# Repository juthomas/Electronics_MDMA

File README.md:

# MEGA DRINKING MACHINA ADVENTURE

<br/>

__Sommaire__ :
* [Description](#description)
* [Installation](#installation-avr)
* [Usage](#usage)
* [Visual Studio Code Linter](#visual-studio-code-linter)
* [Project Functionalities](#project-functionalities)
  * [Leds Control](#leds-control)
  * [Prerequisites](#prerequisites)
  * [Leds Variables](#leds-variables)
  * [Color Attribution](#color-attribution)
  * [Usefull Functions](#usefull-functions)

<div id='description'/>

## Description

Cet objet à été conçu sur les bases d’un témoignage perturbant à la date du 27 juin 2007 sur le forum ████ par l’utilisateur Chri████4.
Il y fait mention d’un jeu à boire avec ses amis où ils auraient décidé d'invoquer Satan aux alentours de 23h42. La soirée aurait tourné en une cruelle mission de subjugation du malin avec pour seule arme l’alcool en grande quantité qu’ils avaient préparé pour faire la fête. Suite à cette affaire le service d’exorcisme V-696 (avec à sa tête Jean-███II) aurait procédé à une énorme commande de Sobieski. 

À travers le projet Mega Drinking Machina Adventure™ nous voulons faire vivre à nos très chers futurs utilisateurs une simulation familiale de cette aventure hors du commun. Une compilation de jeux à boire allant de 1 à 5 joueurs sera proposée, avec une mise en place intuitive et rapide. Sur batterie, lumineux et facile à transporter, il deviendra votre meilleur outil pour pimenter vos soirées peu importe le contexte.
<div id='installation-avr'/>

## Installation (AVR)

* Debian Based Linux :  
  * Install avr-gcc :  
  `sudo apt-get install gcc-avr binutils-avr avr-libc`
  * Install avr-dude :  
  `sudo apt-get install avrdude`
* Macos Unix :  
  * Install brew (for noobies) :  
  `rm -rf $HOME/.brew && git clone --depth=1 https://github.com/Homebrew/brew $HOME/.brew && export PATH=$HOME/.brew/bin:$PATH && brew update && echo "export PATH=$HOME/.brew/bin:$PATH" >> ~/.zshrc`
  * Install avr-gcc :  
  `brew tap osx-cross/avr`  
  `brew install avr-gcc`
  * Install avr-dude :  
  `brew install avrdude`
<div id='usage'/>

## Usage

* Setup port :  
  `ls /dev/ > /tmp/file1`  
  then connect board  
  `ls /dev/ > /tmp/file2`  
  `diff /tmp/file1 /tmp/file2`  
  will give you the port  
  paste the given port to the `PORT` variable of the makefile

* Upload to board :  
  `make coffee` for build and upload  
  `make debug` for debuging  
  `make help` for other options
<div id='visual-studio-code-linter'/>

## Visual Studio Code Linter

* Install C/C++ extension  
* Configure C/C++ extension for avr :  
  Type `C/C++: Edit Configurations (JSON)` in Command Palette  
  * Linux :  
  Add `"/usr/lib/avr/include/**"` line to includePath  
  * Macos :  
  Add `"/Users/tmp/.brew/Cellar/avr-gcc@9/9.3.0_2/avr/include/**"`  
  on labelec macs  
  or  
  `/System/Volumes/Data/usr/local/Cellar/avr-gcc@9/9.3.0_2/avr/include/**`  
  (on real macs)  
  to includePath.  
  If this line doesnt work find "avr/io.h" file with `find / -name io.h`  
  Add the containing folder to includePath (like Linux method)

<div id='project-functionalities'/>

## Project Functionalities

<div id='leds-control'/>

### Leds Control

<div id='prerequisites'/>

#### Prerequisites
* `ft_pin_mode(led_pin, FT_OUTPUT);`

<div id='leds-variables'/>

#### Leds Variables
* char buffer (size = number of leds * 3)

<div id='color-attribution'/>

#### Color Attribution
  The color format is uint32_t : `0xLLRRGGBB`  
  LL : Luminosity (0x01 to 0xFF, or 0x00 to ignore)  
  RR : Red (0x00 to 0xFF)  
  GG : Green (0x00 to 0xFF)  
  BB : Blue (0x00 to 0xFF)  

<div id='usefull-functions'/>

#### Usefull Functions
* `uint8_t *feed_one_pixel(uint16_t pixel_index, uint8_t *pixels, uint32_t color)`  
  feed the selected pixel with the color
* `led_send_data(51, pixels, pixels_number);`  
  send data to the leds

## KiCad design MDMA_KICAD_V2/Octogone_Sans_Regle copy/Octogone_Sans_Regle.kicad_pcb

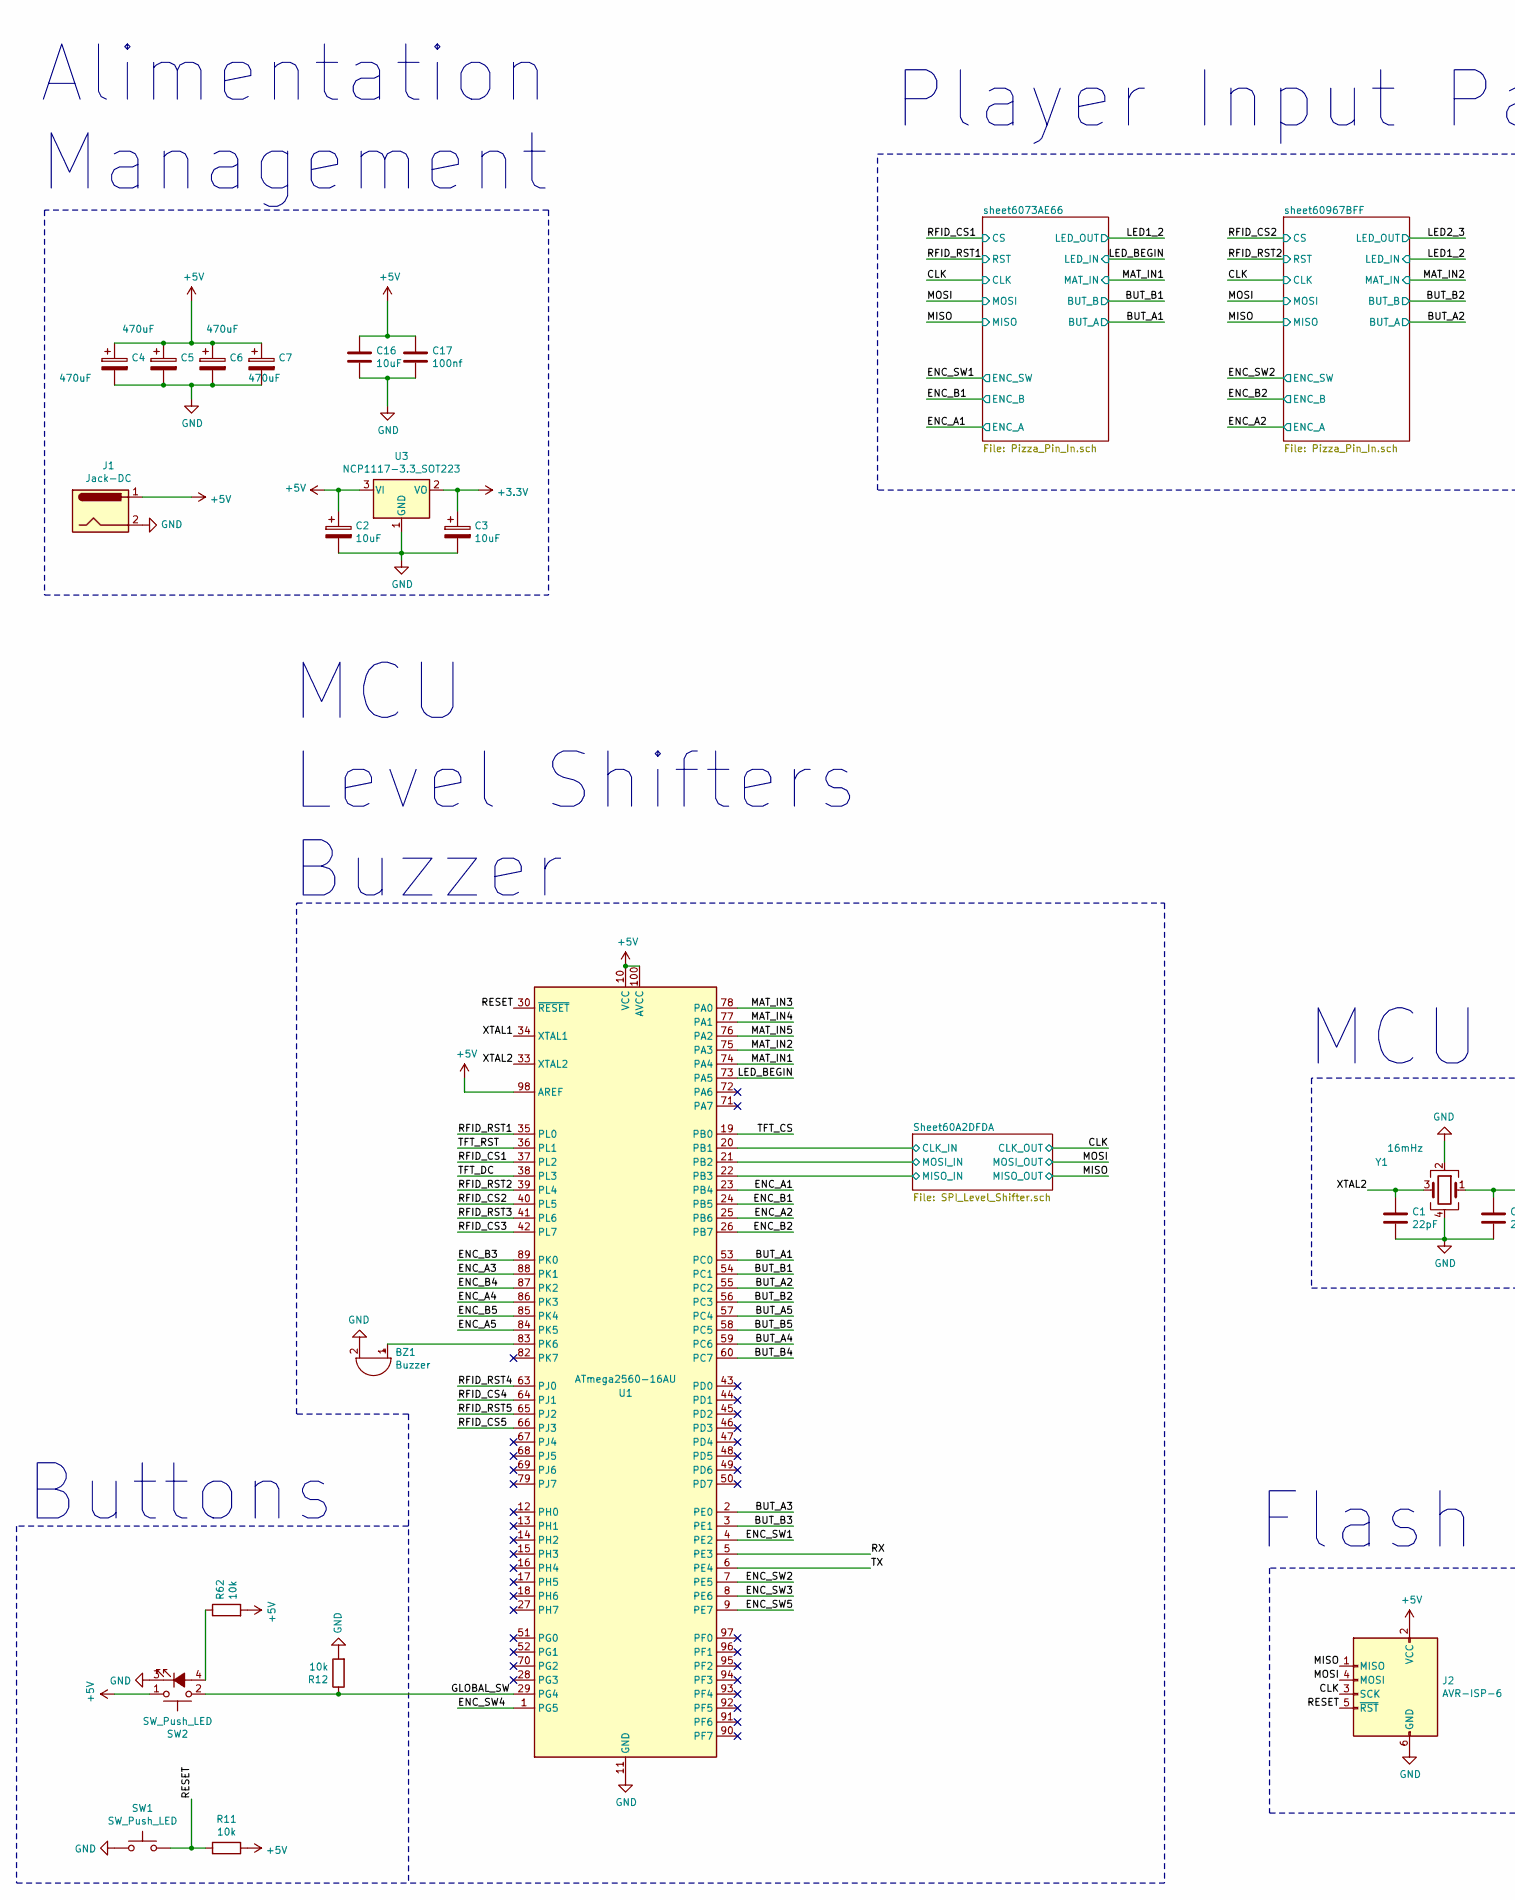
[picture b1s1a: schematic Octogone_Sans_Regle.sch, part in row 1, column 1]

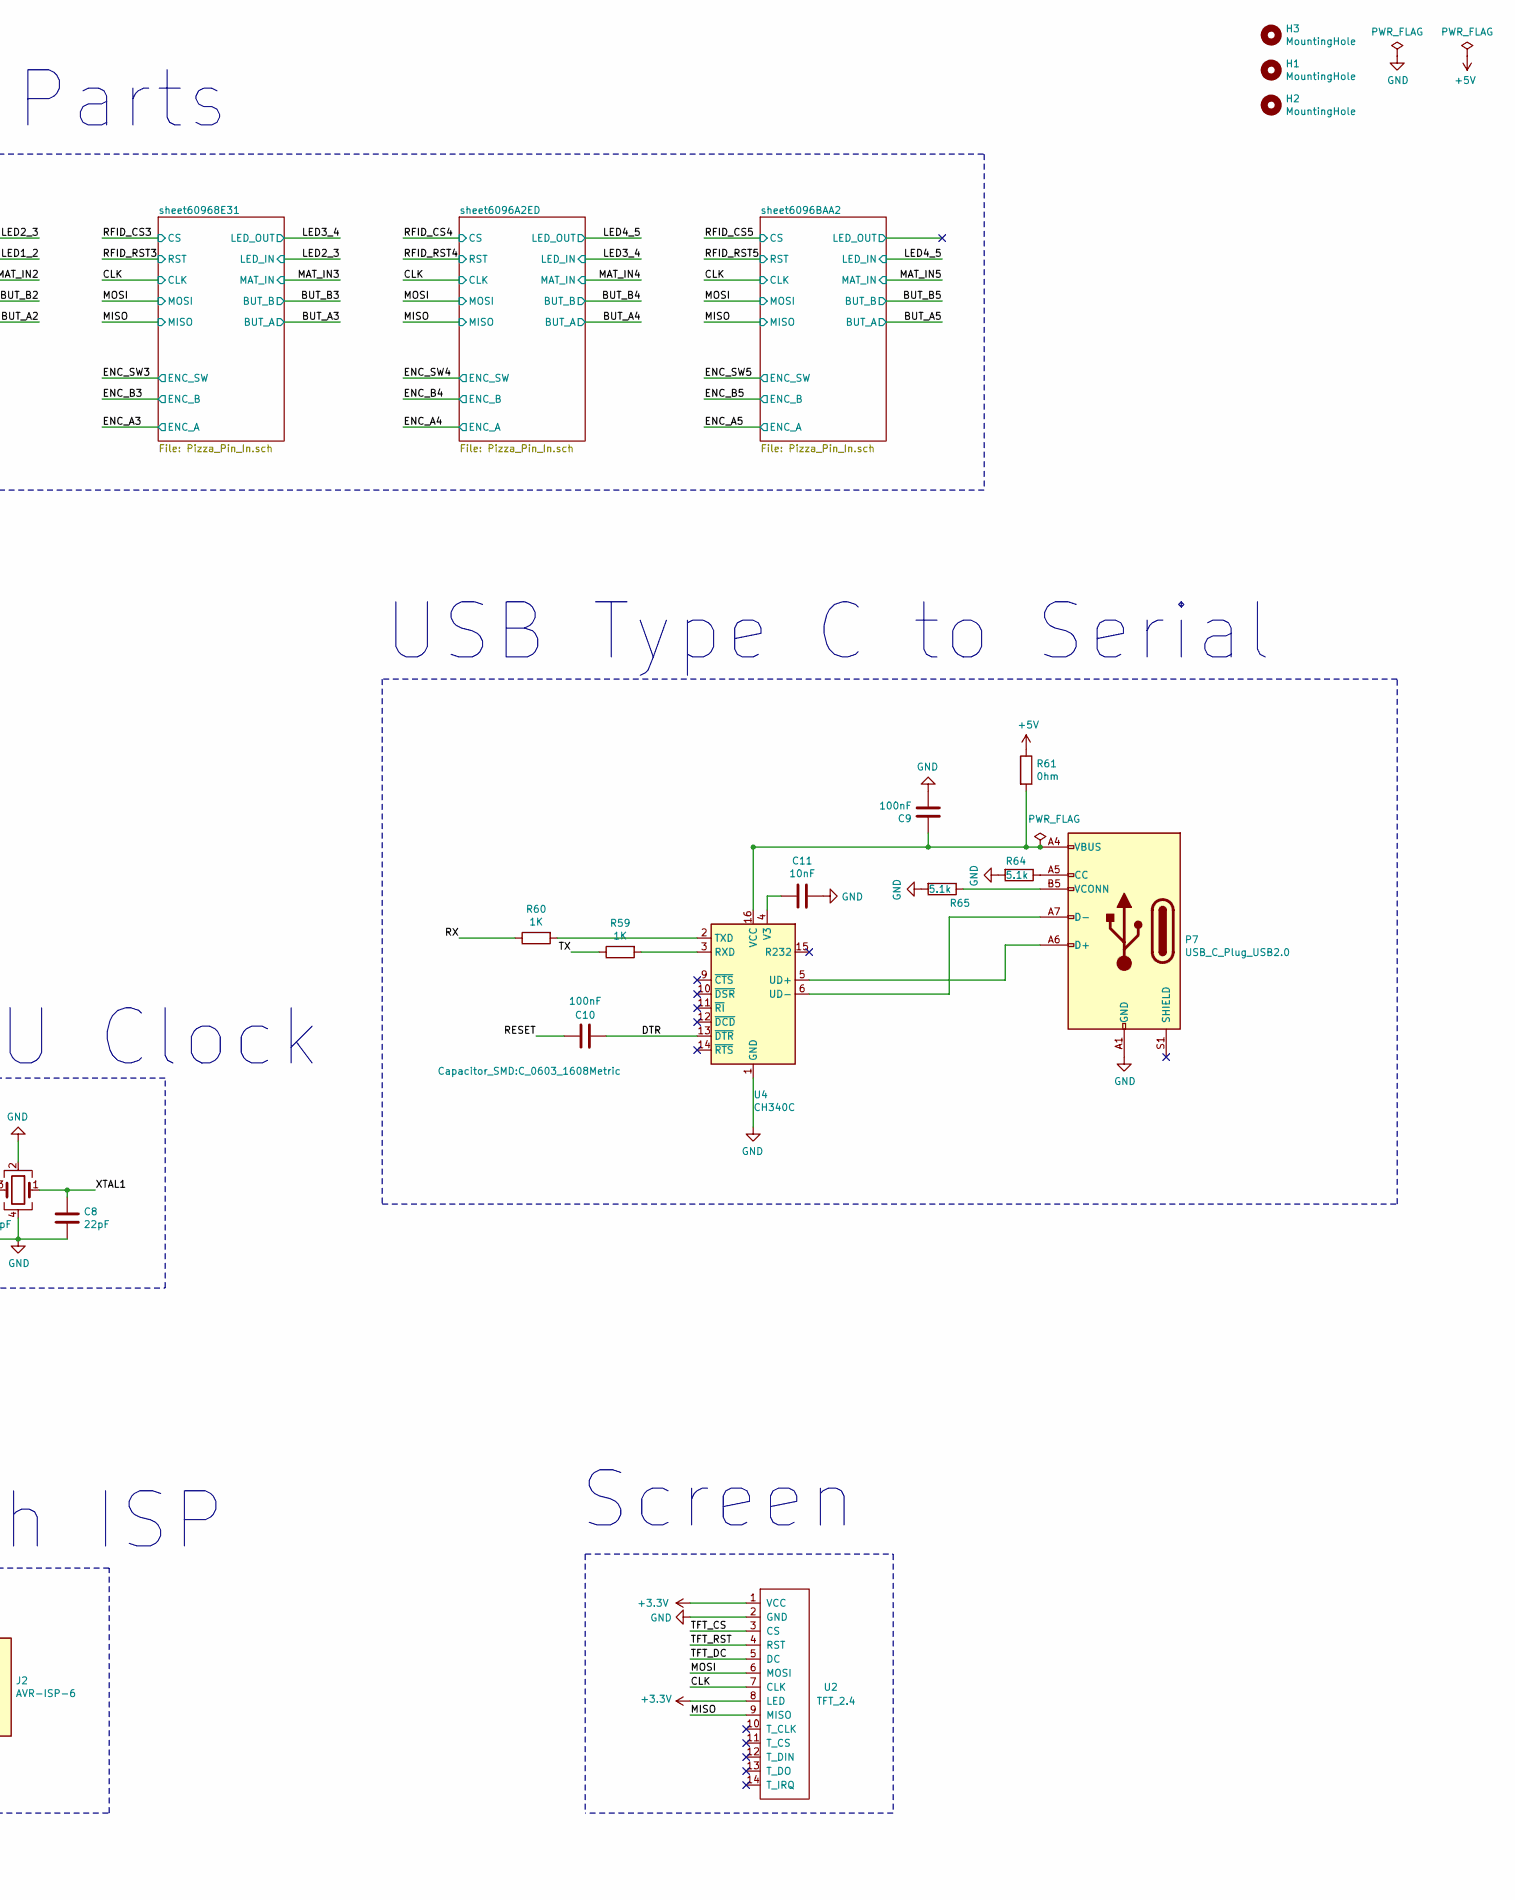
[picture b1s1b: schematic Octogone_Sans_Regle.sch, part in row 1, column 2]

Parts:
BZ1: Buzzer; Buzzer_12x9.5RM7.6
C1, C8: 22pF; C_0603_1608Metric
C2, C3: 10uF; CP_EIA-3216-18_Kemet-A
C4, C5, C6, C7: 470uF; CP_EIA-7343-30_AVX-N
C9, C10: 100nF; C_0603_1608Metric
C11: 10nF; C_0603_1608Metric
C16: 10uF; C_0603_1608Metric
C17: 100nf; C_0603_1608Metric
H1, H2, H3: MountingHole; MountingHole_3.2mm_M3
J1: Jack-DC; BarrelJack_Horizontal
J2: AVR-ISP-6; Connector_SPI_6
P7: USB_C_Plug_USB2.0; USB_C_Receptacle_HRO_TYPE-C-31-M-12
R11, R12, R62: 10k; R_0603_1608Metric
R59, R60: 1K; R_0603_1608Metric
R61: 0hm; R_0603_1608Metric
R64, R65: 5.1k; R_0603_1608Metric
SW1: SW_Push_LED; Switch_4x3
SW2: SW_Push_LED; SW_LED_16mm
U1: ATmega2560-16AU; TQFP-100_14x14mm_P0.5mm
U2: TFT_2.4; TFT_Connector
U3: NCP1117-3.3_SOT223; SOT-223-3_TabPin2
U4: CH340C; SOIC-16_3.9x9.9mm_P1.27mm
Y1: 16mHz; crystal

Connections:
+3V3: C3.1, U2.1 (VCC), U2.8 (LED), U3.2 (VO); also elsewhere on the board
+5V: C2.1, C4.1, C5.1, C6.1, C7.1, C16.1, C17.1, J1.1, J2.2 (VCC), R11.1, R61.1, R62.2, SW2.1, U1.10 (VCC), U1.31 (VCC), U1.61 (VCC), U1.80 (VCC), U1.98 (AREF), U1.100 (AVCC), U3.3 (VI); also elsewhere on the board
/BUT_A1: U1.53 (PC0); also elsewhere on the board
/BUT_A2: U1.55 (PC2); also elsewhere on the board
/BUT_A3: U1.2 (PE0); also elsewhere on the board
/BUT_A4: U1.59 (PC6); also elsewhere on the board
/BUT_A5: U1.57 (PC4); also elsewhere on the board
/BUT_B1: U1.54 (PC1); also elsewhere on the board
/BUT_B2: U1.56 (PC3); also elsewhere on the board
/BUT_B3: U1.3 (PE1); also elsewhere on the board
/BUT_B4: U1.60 (PC7); also elsewhere on the board
/BUT_B5: U1.58 (PC5); also elsewhere on the board
/CLK: J2.3 (SCK), U2.7 (CLK); also elsewhere on the board
/DTR: C10.2, U4.13 (~DTR)
/ENC_A1: U1.23 (PB4); also elsewhere on the board
/ENC_A2: U1.25 (PB6); also elsewhere on the board
/ENC_A3: U1.88 (PK1); also elsewhere on the board
/ENC_A4: U1.86 (PK3); also elsewhere on the board
/ENC_A5: U1.84 (PK5); also elsewhere on the board
/ENC_B1: U1.24 (PB5); also elsewhere on the board
/ENC_B2: U1.26 (PB7); also elsewhere on the board
/ENC_B3: U1.89 (PK0); also elsewhere on the board
/ENC_B4: U1.87 (PK2); also elsewhere on the board
/ENC_B5: U1.85 (PK4); also elsewhere on the board
/ENC_SW1: U1.4 (PE2); also elsewhere on the board
/ENC_SW2: U1.7 (PE5); also elsewhere on the board
/ENC_SW3: U1.8 (PE6); also elsewhere on the board
/ENC_SW4: U1.1 (PG5); also elsewhere on the board
/ENC_SW5: U1.9 (PE7); also elsewhere on the board
/GLOBAL_SW: R12.1, SW2.2, U1.29 (PG4)
/LED_BEGIN: U1.73 (PA5); also elsewhere on the board
/MAT_IN1: U1.74 (PA4); also elsewhere on the board
/MAT_IN2: U1.75 (PA3); also elsewhere on the board
/MAT_IN3: U1.78 (PA0); also elsewhere on the board
/MAT_IN4: U1.77 (PA1); also elsewhere on the board
/MAT_IN5: U1.76 (PA2); also elsewhere on the board
/MISO: J2.1 (MISO), U2.9 (MISO); also elsewhere on the board
/MOSI: J2.4 (MOSI), U2.6 (MOSI); also elsewhere on the board
/RESET: C10.1, J2.5 (~RST), R11.2, SW1.2, U1.30 (~RESET)
/RFID_CS1: U1.37 (PL2); also elsewhere on the board
/RFID_CS2: U1.40 (PL5); also elsewhere on the board
/RFID_CS3: U1.42 (PL7); also elsewhere on the board
/RFID_CS4: U1.64 (PJ1); also elsewhere on the board
/RFID_CS5: U1.66 (PJ3); also elsewhere on the board
/RFID_RST1: U1.35 (PL0); also elsewhere on the board
/RFID_RST2: U1.39 (PL4); also elsewhere on the board
/RFID_RST3: U1.41 (PL6); also elsewhere on the board
/RFID_RST4: U1.63 (PJ0); also elsewhere on the board
/RFID_RST5: U1.65 (PJ2); also elsewhere on the board
/RX: R60.1, U1.5 (PE3)
/Sheet60A2DFDA/CLK_IN: U1.20 (PB1); also elsewhere on the board
/Sheet60A2DFDA/MISO_IN: U1.22 (PB3); also elsewhere on the board
/Sheet60A2DFDA/MOSI_IN: U1.21 (PB2); also elsewhere on the board
/TFT_CS: U1.19 (PB0), U2.3 (CS)
/TFT_DC: U1.38 (PL3), U2.5 (DC)
/TFT_RST: U1.36 (PL1), U2.4 (RST)
/TX: R59.1, U1.6 (PE4)
/XTAL1: C8.1, U1.34 (XTAL1), Y1.1
/XTAL2: C1.1, U1.33 (XTAL2), Y1.3
GND: BZ1.2 (+), C1.2, C2.2, C3.2, C4.2, C5.2, C6.2, C7.2, C8.2, C9.2, C11.2, C16.2, C17.2, J1.2, J2.6 (GND), P7.A1 (GND), P7.A12 (GND), P7.B1 (GND), P7.B12 (GND), R12.2, R64.2, R65.2, SW1.1, SW2.3 (K), U1.11 (GND), U1.32 (GND), U1.62 (GND), U1.81 (GND), U1.99 (GND), U2.2 (GND), U3.1 (GND), U4.1 (GND), Y1.2, Y1.4; also elsewhere on the board
unnamed: BZ1.1 (-), U1.83 (PK6)
unnamed: C9.1, P7.A4 (VBUS), P7.A9 (VBUS), P7.B4 (VBUS), P7.B9 (VBUS), R61.2, U4.16 (VCC)
unnamed: C11.1, U4.4 (V3)
unnamed: P7.A5 (CC), R64.1
unnamed: P7.A6 (D+), U4.5 (UD+)
unnamed: P7.A7 (D-), U4.6 (UD-)
unnamed: P7.B5 (VCONN), R65.1
unnamed: R59.2, U4.3 (RXD)
unnamed: R60.2, U4.2 (TXD)
unnamed: R62.1, SW2.4 (A)

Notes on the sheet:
Player Input Parts
USB Type C to Serial
Screen
Alimentation Management
MCU Clock
Buttons
Flash ISP
MCU Level Shifters Buzzer

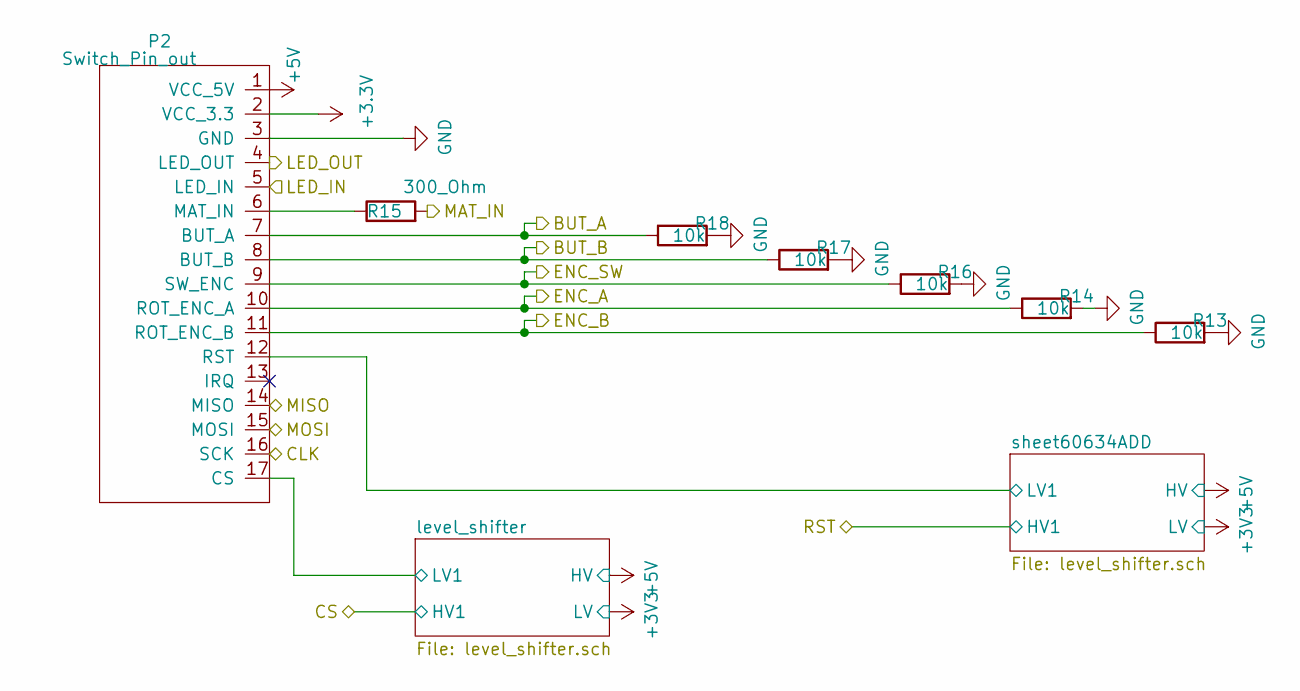
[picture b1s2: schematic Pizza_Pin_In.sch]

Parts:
P1: Switch_Pin_out; Pizza_Pin_Out
R1, R2, R4, R5, R6: 10k; R_0603_1608Metric
R3: 300_Ohm; R_0603_1608Metric

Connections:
+3V3: P1.2 (VCC_3.3); also elsewhere on the board
+5V: P1.1 (VCC_5V); also elsewhere on the board
/BUT_A1: P1.7 (BUT_A), R6.1; also elsewhere on the board
/BUT_B1: P1.8 (BUT_B), R5.1; also elsewhere on the board
/CLK: P1.16 (SCK); also elsewhere on the board
/ENC_A1: P1.10 (ROT_ENC_A), R2.1; also elsewhere on the board
/ENC_B1: P1.11 (ROT_ENC_B), R1.1; also elsewhere on the board
/ENC_SW1: P1.9 (SW_ENC), R4.1; also elsewhere on the board
/LED1_2: P1.4 (LED_OUT); also elsewhere on the board
/LED_BEGIN: P1.5 (LED_IN); also elsewhere on the board
/MAT_IN1: R3.2; also elsewhere on the board
/MISO: P1.14 (MISO); also elsewhere on the board
/MOSI: P1.15 (MOSI); also elsewhere on the board
/sheet6073AE66/level_shifter/LV1: P1.17 (CS); also elsewhere on the board
/sheet6073AE66/sheet60634ADD/LV1: P1.12 (RST); also elsewhere on the board
GND: P1.3 (GND), R1.2, R2.2, R4.2, R5.2, R6.2; also elsewhere on the board
unnamed: P1.6 (MAT_IN), R3.1

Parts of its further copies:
P2, P3, P4, P5: Switch_Pin_out; Pizza_Pin_Out
R13, R14, R16, R17, R18, R23, R24, R26, R27, R28, R39, R40, R42, R43, R44, R49, R50, R52, R53, R54: 10k; R_0603_1608Metric
R15, R25, R41, R51: 300_Ohm; R_0603_1608Metric

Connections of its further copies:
+3V3: P2.2 (VCC_3.3), P3.2 (VCC_3.3), P4.2 (VCC_3.3), P5.2 (VCC_3.3); also elsewhere on the board
+5V: P2.1 (VCC_5V), P3.1 (VCC_5V), P4.1 (VCC_5V), P5.1 (VCC_5V); also elsewhere on the board
/BUT_A2: P5.7 (BUT_A), R54.1; also elsewhere on the board
/BUT_A3: P2.7 (BUT_A), R18.1; also elsewhere on the board
/BUT_A4: P3.7 (BUT_A), R28.1; also elsewhere on the board
/BUT_A5: P4.7 (BUT_A), R44.1; also elsewhere on the board
/BUT_B2: P5.8 (BUT_B), R53.1; also elsewhere on the board
/BUT_B3: P2.8 (BUT_B), R17.1; also elsewhere on the board
/BUT_B4: P3.8 (BUT_B), R27.1; also elsewhere on the board
/BUT_B5: P4.8 (BUT_B), R43.1; also elsewhere on the board
/CLK: P2.16 (SCK), P3.16 (SCK), P4.16 (SCK), P5.16 (SCK); also elsewhere on the board
/ENC_A2: P5.10 (ROT_ENC_A), R50.1; also elsewhere on the board
/ENC_A3: P2.10 (ROT_ENC_A), R14.1; also elsewhere on the board
/ENC_A4: P3.10 (ROT_ENC_A), R24.1; also elsewhere on the board
/ENC_A5: P4.10 (ROT_ENC_A), R40.1; also elsewhere on the board
/ENC_B2: P5.11 (ROT_ENC_B), R49.1; also elsewhere on the board
/ENC_B3: P2.11 (ROT_ENC_B), R13.1; also elsewhere on the board
/ENC_B4: P3.11 (ROT_ENC_B), R23.1; also elsewhere on the board
/ENC_B5: P4.11 (ROT_ENC_B), R39.1; also elsewhere on the board
/ENC_SW2: P5.9 (SW_ENC), R52.1; also elsewhere on the board
/ENC_SW3: P2.9 (SW_ENC), R16.1; also elsewhere on the board
/ENC_SW4: P3.9 (SW_ENC), R26.1; also elsewhere on the board
/ENC_SW5: P4.9 (SW_ENC), R42.1; also elsewhere on the board
/LED1_2: P5.5 (LED_IN); also elsewhere on the board
/LED2_3: P2.5 (LED_IN), P5.4 (LED_OUT)
/LED3_4: P2.4 (LED_OUT), P3.5 (LED_IN)
/LED4_5: P3.4 (LED_OUT), P4.5 (LED_IN)
/MAT_IN2: R51.2; also elsewhere on the board
/MAT_IN3: R15.2; also elsewhere on the board
/MAT_IN4: R25.2; also elsewhere on the board
/MAT_IN5: R41.2; also elsewhere on the board
/MISO: P2.14 (MISO), P3.14 (MISO), P4.14 (MISO), P5.14 (MISO); also elsewhere on the board
/MOSI: P2.15 (MOSI), P3.15 (MOSI), P4.15 (MOSI), P5.15 (MOSI); also elsewhere on the board
/sheet6096A2ED/level_shifter/LV1: P3.17 (CS); also elsewhere on the board
/sheet6096A2ED/sheet60634ADD/LV1: P3.12 (RST); also elsewhere on the board
/sheet6096BAA2/level_shifter/LV1: P4.17 (CS); also elsewhere on the board
/sheet6096BAA2/sheet60634ADD/LV1: P4.12 (RST); also elsewhere on the board
/sheet60967BFF/level_shifter/LV1: P5.17 (CS); also elsewhere on the board
/sheet60967BFF/sheet60634ADD/LV1: P5.12 (RST); also elsewhere on the board
/sheet60968E31/level_shifter/LV1: P2.17 (CS); also elsewhere on the board
/sheet60968E31/sheet60634ADD/LV1: P2.12 (RST); also elsewhere on the board
GND: P2.3 (GND), P3.3 (GND), P4.3 (GND), P5.3 (GND), R13.2, R14.2, R16.2, R17.2, R18.2, R23.2, R24.2, R26.2, R27.2, R28.2, R39.2, R40.2, R42.2, R43.2, R44.2, R49.2, R50.2, R52.2, R53.2, R54.2; also elsewhere on the board
unnamed: P2.6 (MAT_IN), R15.1
unnamed: P3.6 (MAT_IN), R25.1
unnamed: P4.6 (MAT_IN), R41.1
unnamed: P5.6 (MAT_IN), R51.1

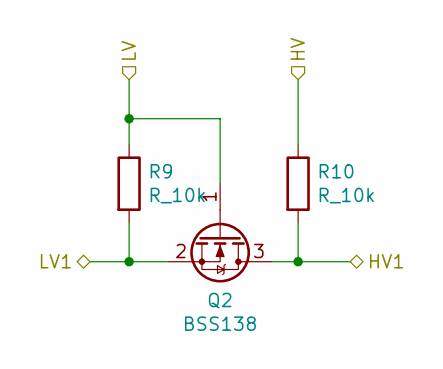
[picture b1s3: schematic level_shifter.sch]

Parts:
Q1: BSS138; SOT-23
R7, R8: R_10k; R_0603_1608Metric

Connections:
+3V3: Q1.1 (G), R7.1; also elsewhere on the board
+5V: R8.1; also elsewhere on the board
/RFID_CS1: Q1.3 (D), R8.2; also elsewhere on the board
/sheet6073AE66/level_shifter/LV1: Q1.2 (S), R7.2; also elsewhere on the board

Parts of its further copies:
Q2, Q3, Q4, Q5, Q6, Q7, Q8, Q9, Q10, Q11, Q12, Q13, Q14: BSS138; SOT-23
R9, R10, R19, R20, R21, R22, R29, R30, R31, R32, R33, R34, R35, R36, R37, R38, R45, R46, R47, R48, R55, R56, R57, R58: R_10k; R_0603_1608Metric

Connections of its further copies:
+3V3: Q2.1 (G), Q4.1 (G), Q5.1 (G), Q6.1 (G), Q7.1 (G), Q8.1 (G), Q9.1 (G), Q10.1 (G), Q11.1 (G), Q12.1 (G), Q13.1 (G), Q14.1 (G), R9.1, R19.1, R21.1, R29.1, R31.1, R33.1, R35.1, R37.1, R45.1, R47.1, R55.1, R57.1; also elsewhere on the board
+5V: R10.1, R20.1, R22.1, R30.1, R32.1, R34.1, R36.1, R38.1, R46.1, R48.1, R56.1, R58.1; also elsewhere on the board
/CLK: Q8.2 (S), R33.2; also elsewhere on the board
/MISO: Q10.2 (S), R37.2; also elsewhere on the board
/MOSI: Q9.2 (S), R35.2; also elsewhere on the board
/RFID_CS2: Q13.3 (D), R56.2; also elsewhere on the board
/RFID_CS3: Q4.3 (D), R20.2; also elsewhere on the board
/RFID_CS4: Q6.3 (D), R30.2; also elsewhere on the board
/RFID_CS5: Q11.3 (D), R46.2; also elsewhere on the board
/RFID_RST1: Q2.3 (D), R10.2; also elsewhere on the board
/RFID_RST2: Q14.3 (D), R58.2; also elsewhere on the board
/RFID_RST3: Q5.3 (D), R22.2; also elsewhere on the board
/RFID_RST4: Q7.3 (D), R32.2; also elsewhere on the board
/RFID_RST5: Q12.3 (D), R48.2; also elsewhere on the board
/Sheet60A2DFDA/CLK_IN: Q8.3 (D), R34.2; also elsewhere on the board
/Sheet60A2DFDA/MISO_IN: Q10.3 (D), R38.2; also elsewhere on the board
/Sheet60A2DFDA/MOSI_IN: Q9.3 (D), R36.2; also elsewhere on the board
/sheet6073AE66/sheet60634ADD/LV1: Q2.2 (S), R9.2; also elsewhere on the board
/sheet6096A2ED/level_shifter/LV1: Q6.2 (S), R29.2; also elsewhere on the board
/sheet6096A2ED/sheet60634ADD/LV1: Q7.2 (S), R31.2; also elsewhere on the board
/sheet6096BAA2/level_shifter/LV1: Q11.2 (S), R45.2; also elsewhere on the board
/sheet6096BAA2/sheet60634ADD/LV1: Q12.2 (S), R47.2; also elsewhere on the board
/sheet60967BFF/level_shifter/LV1: Q13.2 (S), R55.2; also elsewhere on the board
/sheet60967BFF/sheet60634ADD/LV1: Q14.2 (S), R57.2; also elsewhere on the board
/sheet60968E31/level_shifter/LV1: Q4.2 (S), R19.2; also elsewhere on the board
/sheet60968E31/sheet60634ADD/LV1: Q5.2 (S), R21.2; also elsewhere on the board

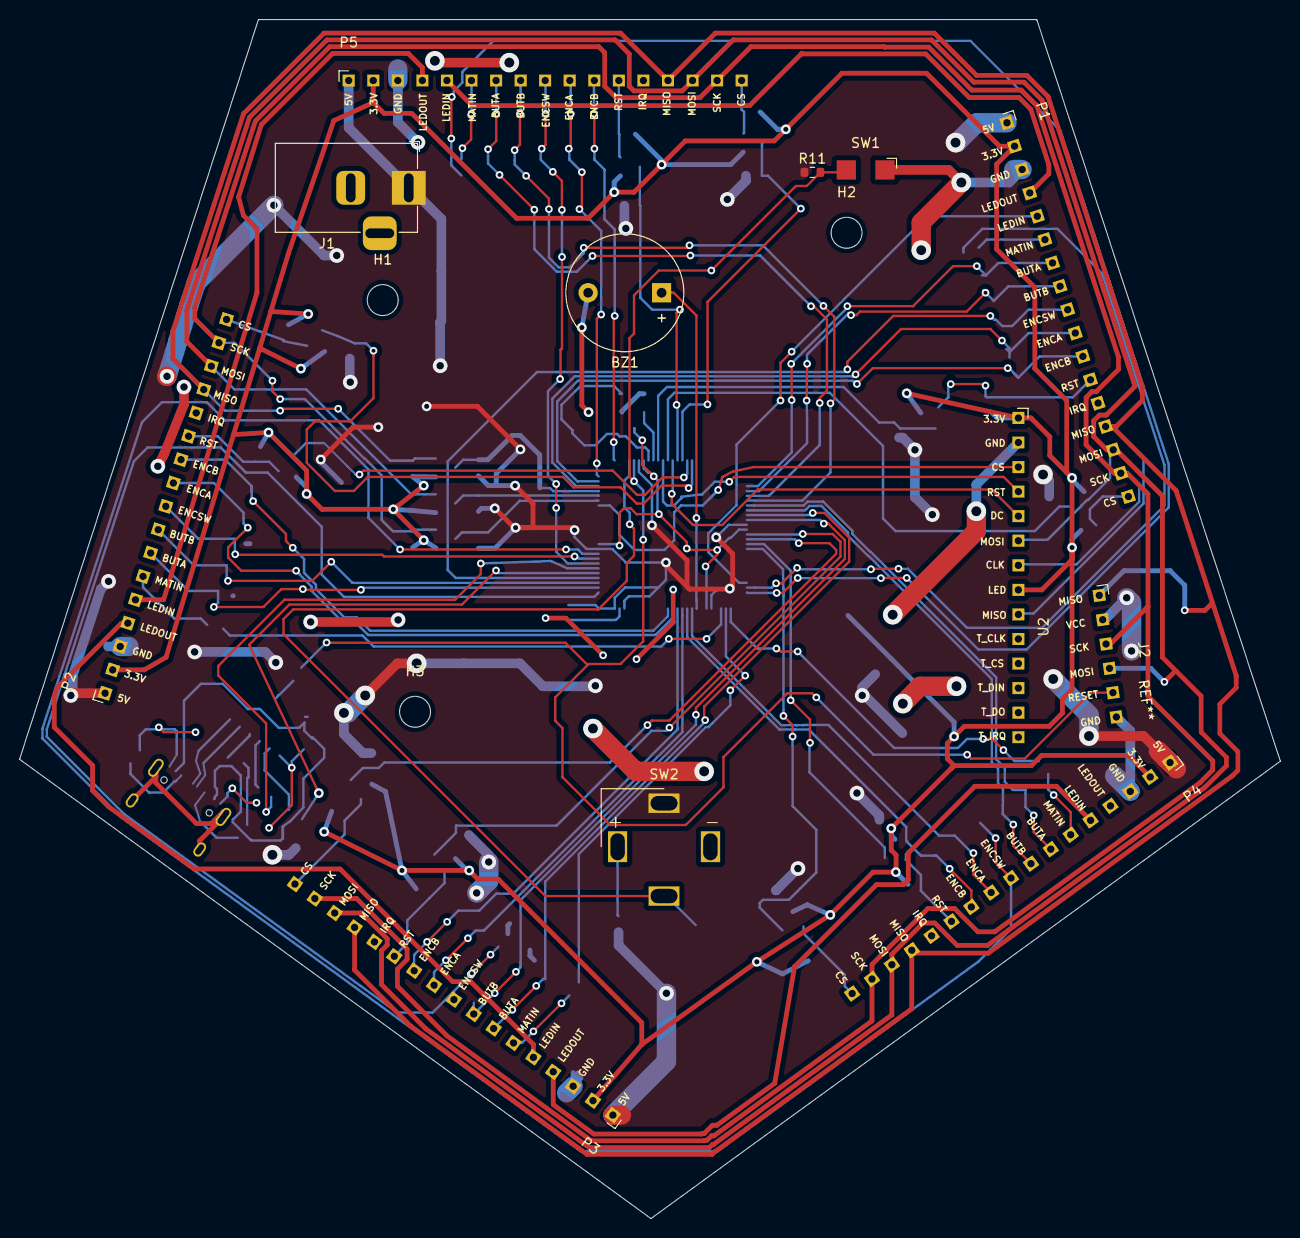
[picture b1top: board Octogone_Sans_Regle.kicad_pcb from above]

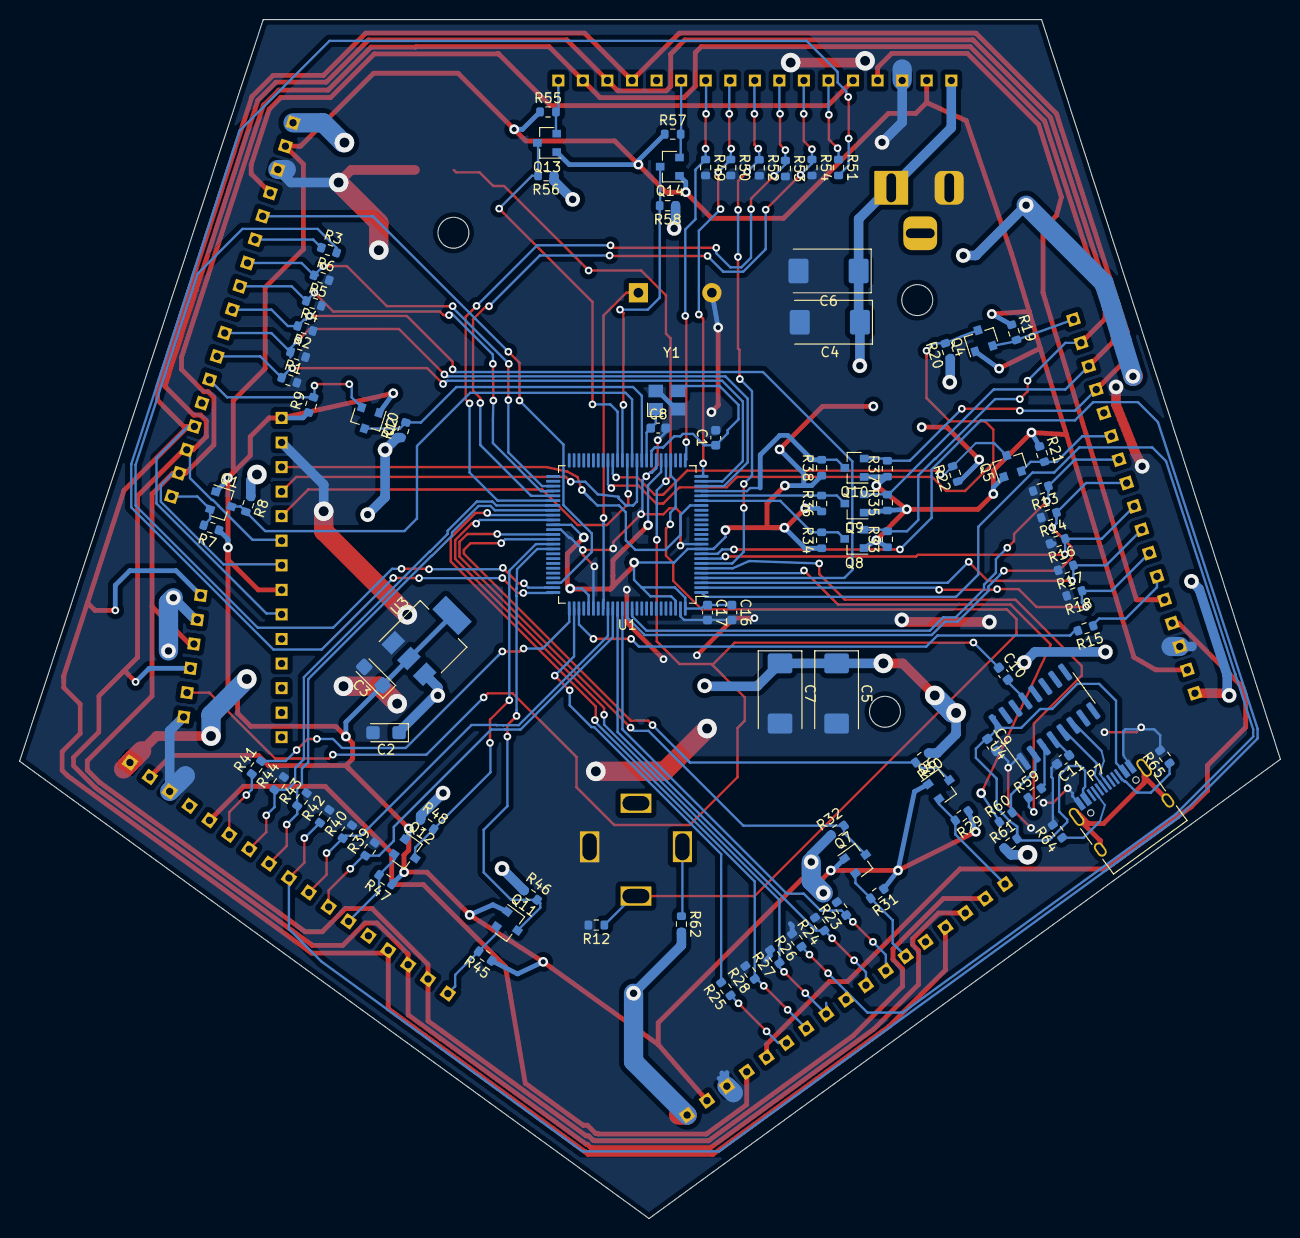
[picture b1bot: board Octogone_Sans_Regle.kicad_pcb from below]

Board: 2 copper layers, 130.4 x 124.0 mm, 109 parts (94 on the bottom side), 89 nets.
